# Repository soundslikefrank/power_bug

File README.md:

# power_bug
Eurorack PSU for tiny skiffs and prototyping (5V input)

## License

cc-by-sa-4.0

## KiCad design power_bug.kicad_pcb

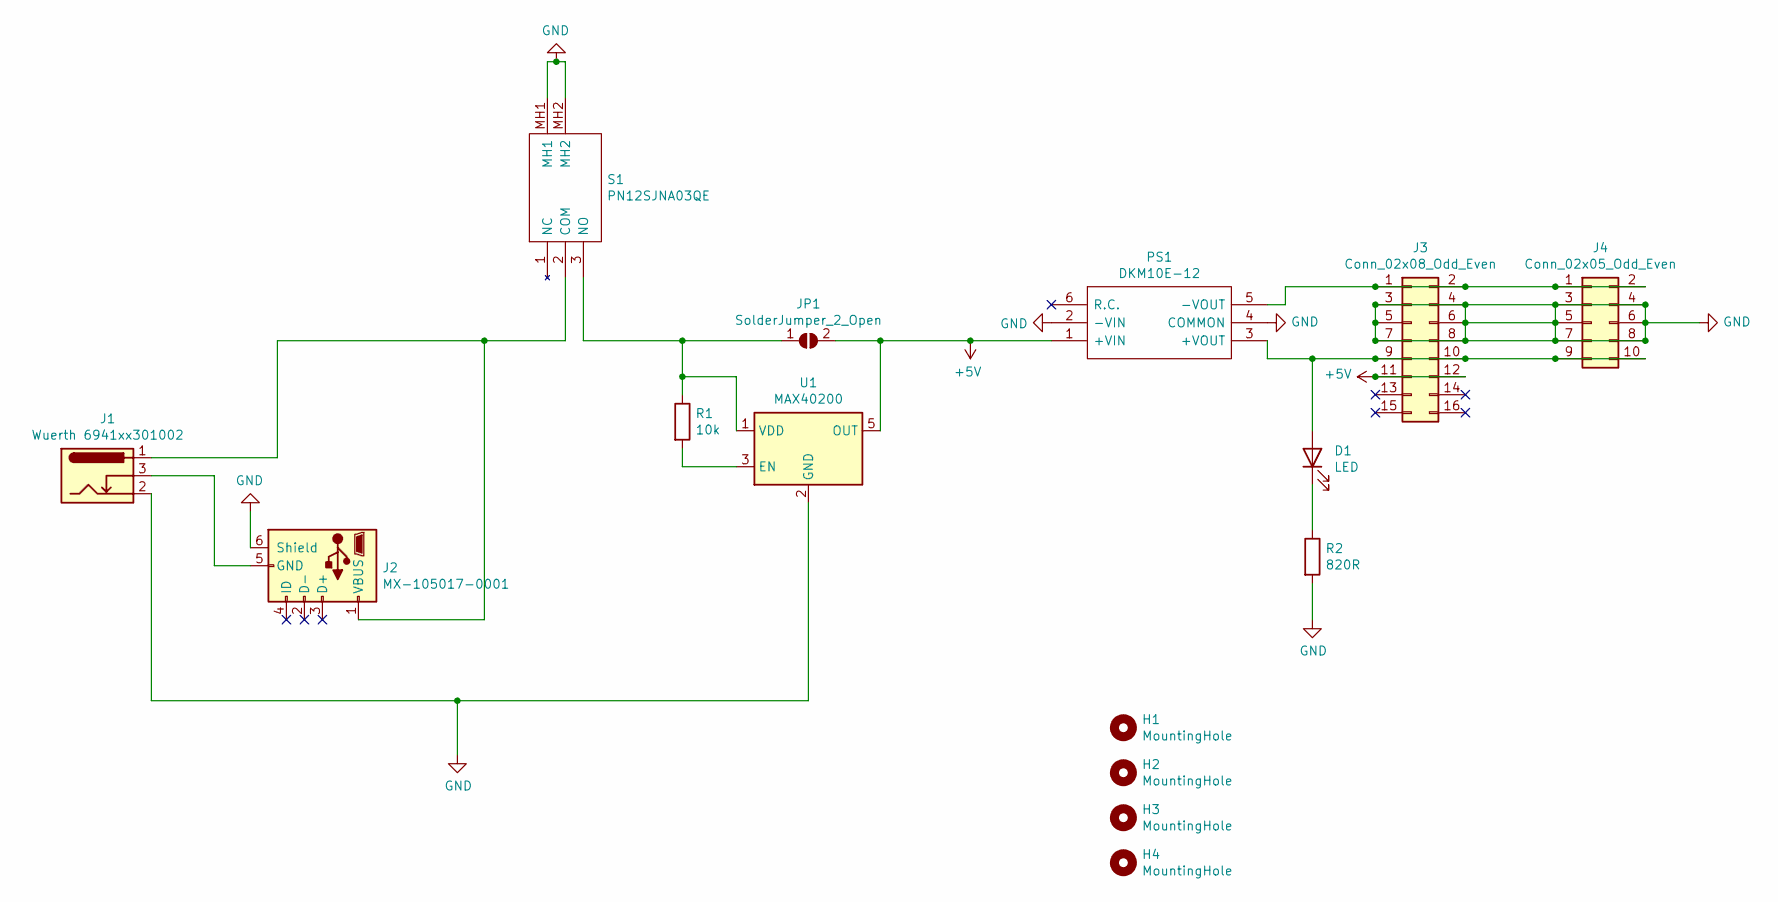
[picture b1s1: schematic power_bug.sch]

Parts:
D1: LED; LED_D3.0mm
H1, H2, H3, H4: MountingHole; MountingHole_3.2mm_M3
J1: Wuerth 6941xx301002; BarrelJack_Wuerth_6941xx301002
J2: MX-105017-0001; USB_Micro-B_Molex-105017-0001
J3: Conn_02x08_Odd_Even; IDC-Header_2x08_P2.54mm_Vertical
J4: Conn_02x05_Odd_Even; PinSocket_2x05_P2.54mm_Vertical
JP1: SolderJumper_2_Open; SolderJumper-2_P1.3mm_Open_RoundedPad1.0x1.5mm
PS1: DKM10E-12; DKM10E12; Manufacturer_Part_Number DKM10E-12; Mouser Part Number 709-DKM10E-12
R1: 10k; R_0603_1608Metric_Pad1.05x0.95mm_HandSolder
R2: 820R; R_0603_1608Metric_Pad1.05x0.95mm_HandSolder
S1: PN12SJNA03QE; Manufacturer_Part_Number PN12SJNA03QE; Mouser Part Number 611-PN12SJNA03QE
U1: MAX40200; SOT-23-5

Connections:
+5V: J3.11, J3.12, JP1.2 (B), PS1.1 (+VIN), U1.5 (OUT)
GND: J1.2, J2.6 (Shield), J3.3, J3.4, J3.5, J3.6, J3.7, J3.8, J4.3, J4.4, J4.5, J4.6, J4.7, J4.8, PS1.2 (-VIN), PS1.4 (COMMON), R2.2, S1.MH1, S1.MH2, U1.2 (GND)
unnamed: D1.1 (K), R2.1
unnamed: D1.2 (A), J3.9, J3.10, J4.9, J4.10, PS1.3 (+VOUT)
unnamed: J1.1, J2.1 (VBUS), S1.2 (COM)
unnamed: J1.3, J2.5 (GND)
unnamed: J3.1, J3.2, J4.1, J4.2, PS1.5 (-VOUT)
unnamed: JP1.1 (A), R1.1, S1.3 (NO), U1.1 (VDD)
unnamed: R1.2, U1.3 (EN)

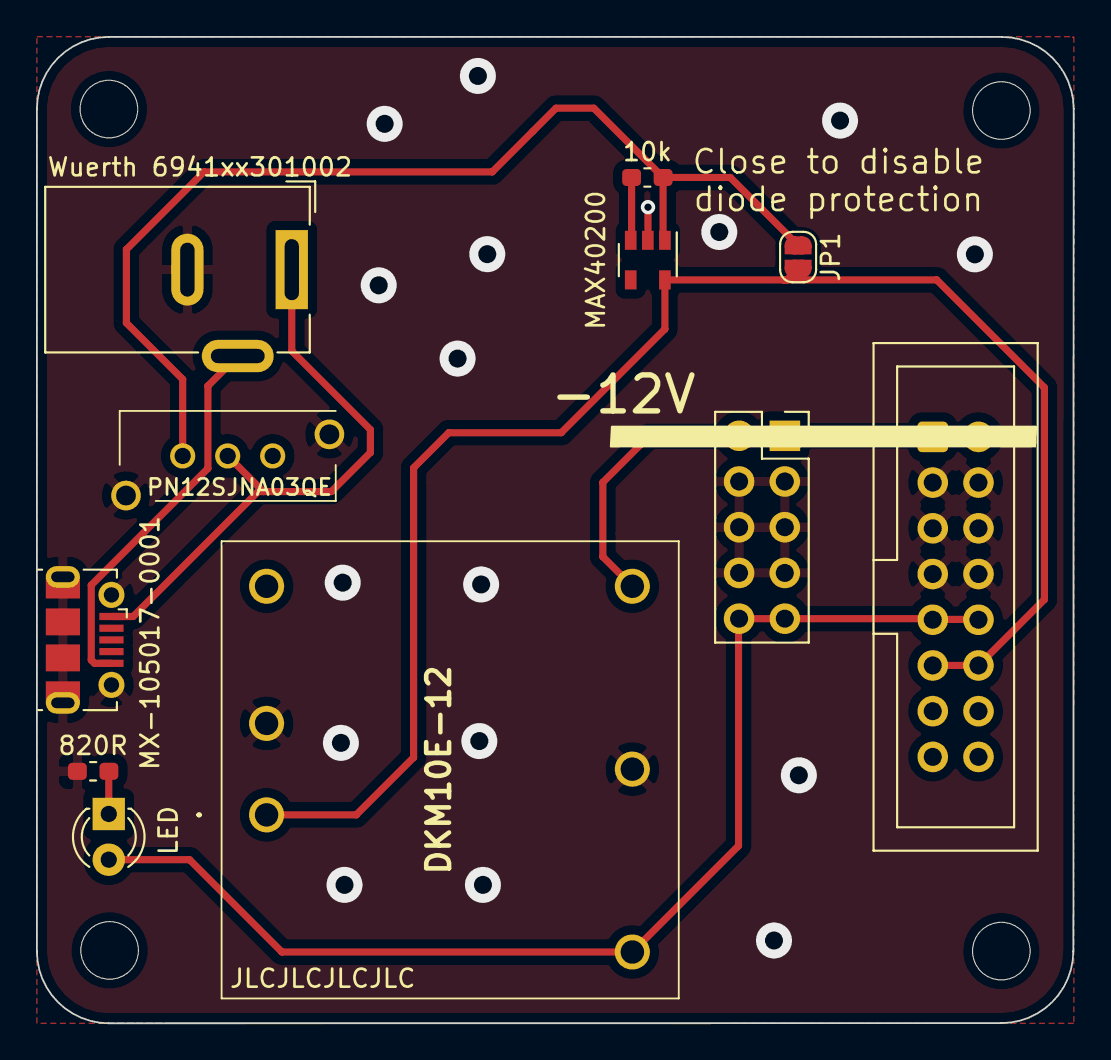
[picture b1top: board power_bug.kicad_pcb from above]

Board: 2 copper layers, 57.6 x 54.8 mm, 15 parts (0 on the bottom side), 9 nets.
